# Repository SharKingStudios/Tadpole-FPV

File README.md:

# Tadpole FPV Drone
A small FPV drone that has a custom cost effective transmitter PCB.

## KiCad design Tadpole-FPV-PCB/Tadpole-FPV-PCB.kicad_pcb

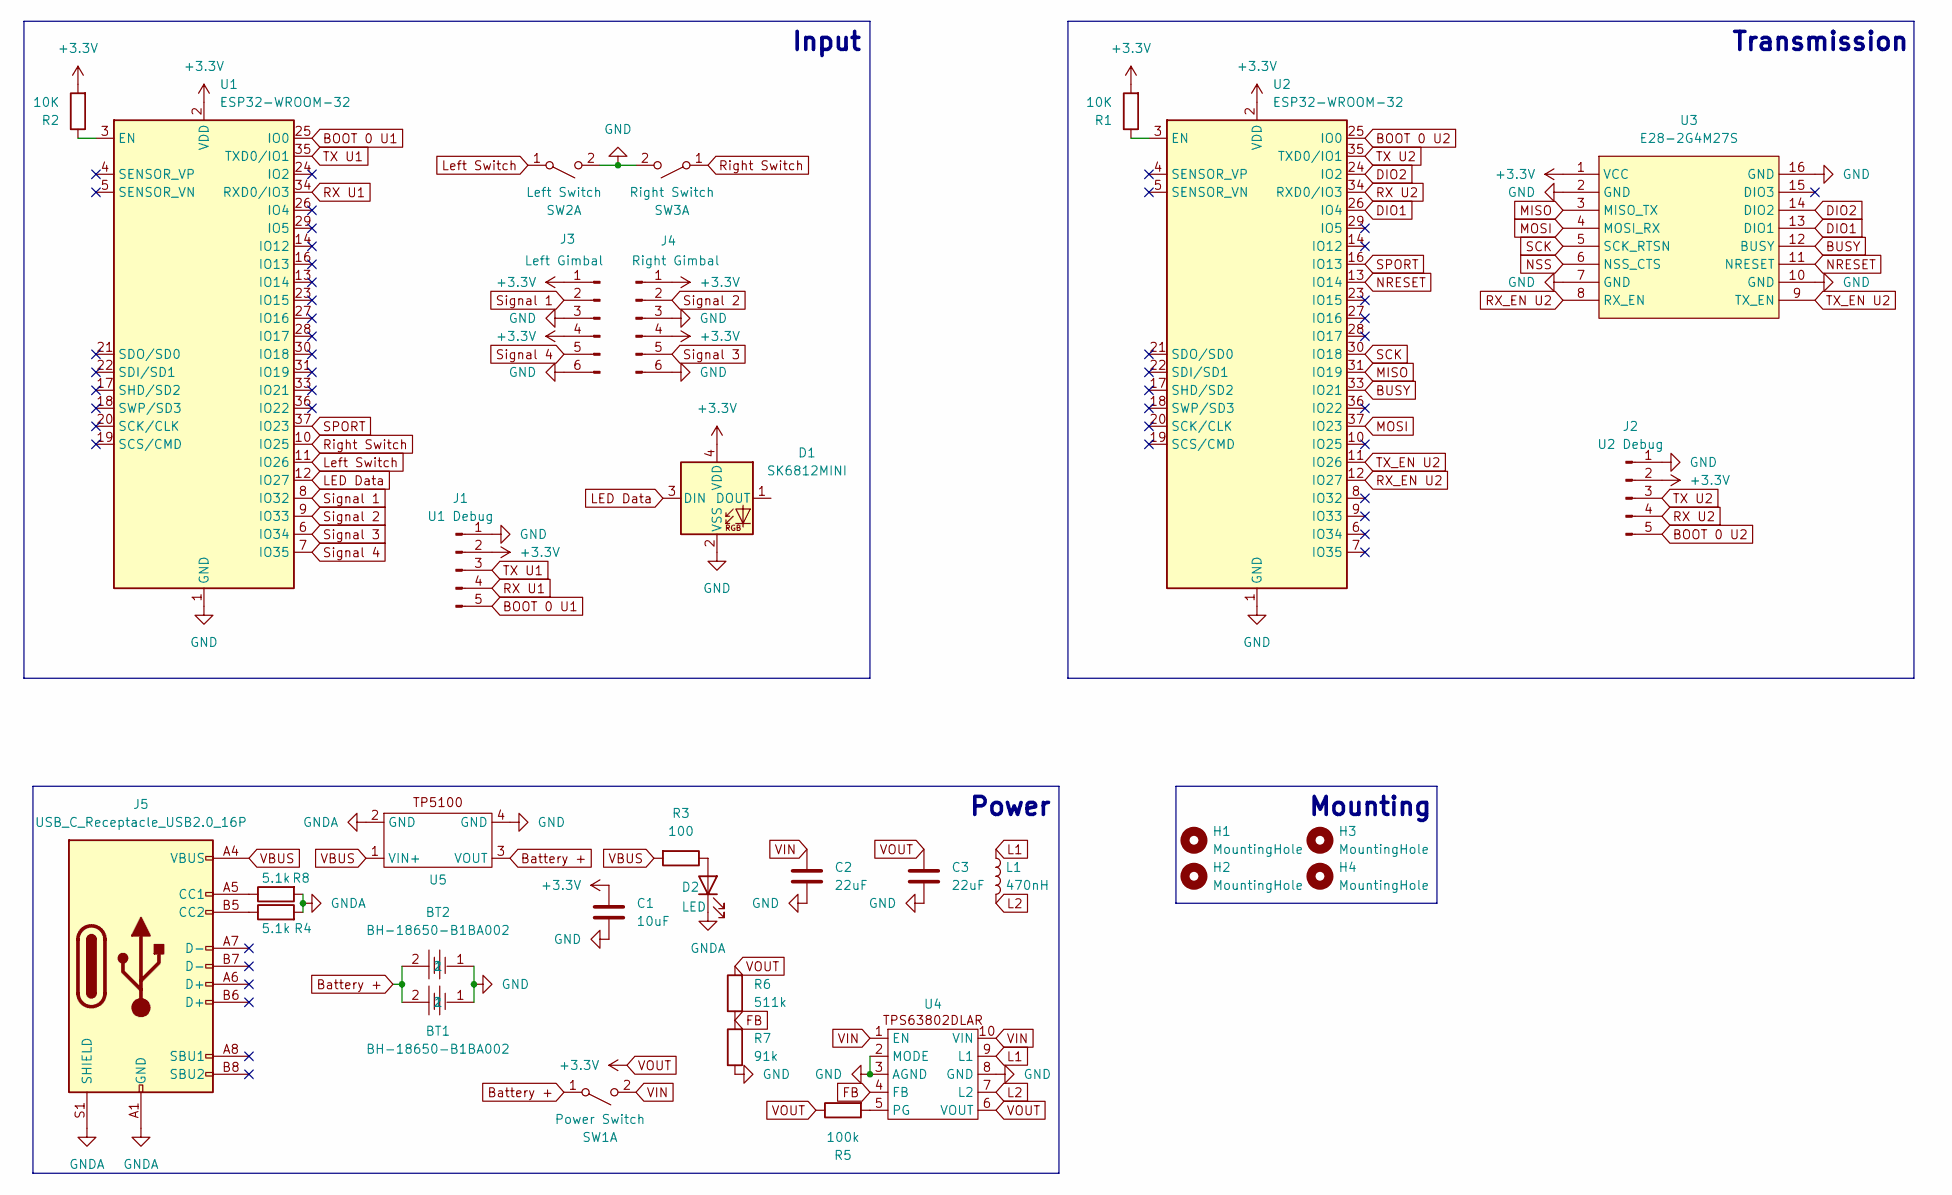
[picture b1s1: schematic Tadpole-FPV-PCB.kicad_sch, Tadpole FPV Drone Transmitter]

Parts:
BT1, BT2: BH-18650-B1BA002; BATTERY-SMD_18650-1S-L77.1-W20.7-1; LCSC Part C2988620
C1: 10uF; CP_Radial_D5.0mm_P2.50mm
C2, C3: 22uF; C_0603_1608Metric
D1: SK6812MINI; LED_SK6812MINI_PLCC4_3.5x3.5mm_P1.75mm
D2: LED; 0603 LED
H1, H2, H3, H4: MountingHole; MountingHole_3.2mm_M3_Pad_Via
J1: U1 Debug; PinHeader_1x05_P2.54mm_Vertical
J2: U2 Debug; PinHeader_1x05_P2.54mm_Vertical
J3: Left Gimbal; PinHeader_1x06_P2.54mm_Vertical
J4: Right Gimbal; PinHeader_1x06_P2.54mm_Vertical
J5: USB_C_Receptacle_USB2.0_16P; USB_C_Receptacle_GCT_USB4105-xx-A_16P_TopMnt_Horizontal
L1: 470nH; IND-SMD_L4.0-W4.0_XGL4020
R1, R2: 10K; R_0603_1608Metric
R3: 100; R_0603_1608Metric
R4, R8: 5.1k; R_0603_1608Metric
R5: 100k; R_0402_1005Metric
R6: 511k; R_0402_1005Metric
R7: 91k; R_0603_1608Metric
SW1: Power Switch; PinHeader_1x02_P2.54mm_Vertical
SW2: Left Switch; PinHeader_1x02_P2.54mm_Vertical
SW3: Right Switch; PinHeader_1x02_P2.54mm_Vertical
U1, U2: ESP32-WROOM-32
U3: E28-2G4M27S; WIRELM-SMD_E28-2G4M2XS; LCSC Part C411312
U4: VSON-10_L3.0-W2.0-P0.50-TL
U5: TP5100

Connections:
BOOT 0 U1: J1.5, U1.25 (IO0)
BOOT 0 U2: J2.5, U2.25 (IO0)
BUSY: U2.33 (IO21), U3.12 (BUSY)
Battery +: BT1.2, BT2.2, SW1.1 (A), U5.3 (VOUT)
DIO1: U2.26 (IO4), U3.13 (DIO1)
DIO2: U2.24 (IO2), U3.14 (DIO2)
FB: R6.1, R7.2, U4.4 (FB)
GND: BT1.1, BT2.1, C1.2, C2.1, C3.2, D1.2 (VSS), J1.1, J2.1, J3.3, J3.6, J4.3, J4.6, R7.1, SW2.2 (B), SW3.2 (B), U1.1 (GND), U1.15 (GND), U1.38 (GND), U1.39 (GND), U2.1 (GND), U2.15 (GND), U2.38 (GND), U2.39 (GND), U3.2 (GND), U3.7 (GND), U3.10 (GND), U3.16 (GND), U4.2 (MODE), U4.3 (AGND), U4.8 (GND), U5.4 (GND)
GNDA: D2.1 (K), J5.A1 (GND), J5.A12 (GND), J5.B1 (GND), J5.B12 (GND), J5.S1 (SHIELD), R4.2, R8.2, U5.2 (GND)
L1: L1.1, U4.9 (L1)
L2: L1.2, U4.7 (L2)
LED Data: D1.3 (DIN), U1.12 (IO27)
Left Switch: SW2.1 (A), U1.11 (IO26)
MISO: U2.31 (IO19), U3.3 (MISO_TX)
MOSI: U2.37 (IO23), U3.4 (MOSI_RX)
NRESET: U2.13 (IO14), U3.11 (NRESET)
NSS: U3.6 (NSS_CTS)
unnamed: D2.2 (A), R3.1
unnamed: J5.A5 (CC1), R8.1
unnamed: J5.B5 (CC2), R4.1
unnamed: R2.1, U1.3 (EN)
unnamed: R1.1, U2.3 (EN)
unnamed: R5.2, U4.5 (PG)
RX U1: J1.4, U1.34 (RXD0/IO3)
RX U2: J2.4, U2.34 (RXD0/IO3)
RX_EN U2: U2.12 (IO27), U3.8 (RX_EN)
Right Switch: SW3.1 (A), U1.10 (IO25)
SCK: U2.30 (IO18), U3.5 (SCK_RTSN)
SPORT: U1.37 (IO23), U2.16 (IO13)
Signal 1: J3.2, U1.8 (IO32)
Signal 2: J4.2, U1.9 (IO33)
Signal 3: J4.5, U1.6 (IO34)
Signal 4: J3.5, U1.7 (IO35)
TX U1: J1.3, U1.35 (TXD0/IO1)
TX U2: J2.3, U2.35 (TXD0/IO1)
TX_EN U2: U2.11 (IO26), U3.9 (TX_EN)
VBUS: J5.A4 (VBUS), J5.A9 (VBUS), J5.B4 (VBUS), J5.B9 (VBUS), R3.2, U5.1 (VIN+)
VIN: C2.2, SW1.2 (B), U4.1 (EN), U4.10 (VIN)
VOUT: C1.1, C3.1, D1.4 (VDD), J1.2, J2.2, J3.1, J3.4, J4.1, J4.4, R1.2, R2.2, R5.1, R6.2, U1.2 (VDD), U2.2 (VDD), U3.1 (VCC), U4.6 (VOUT)

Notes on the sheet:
Mounting
Transmission
Input
Power

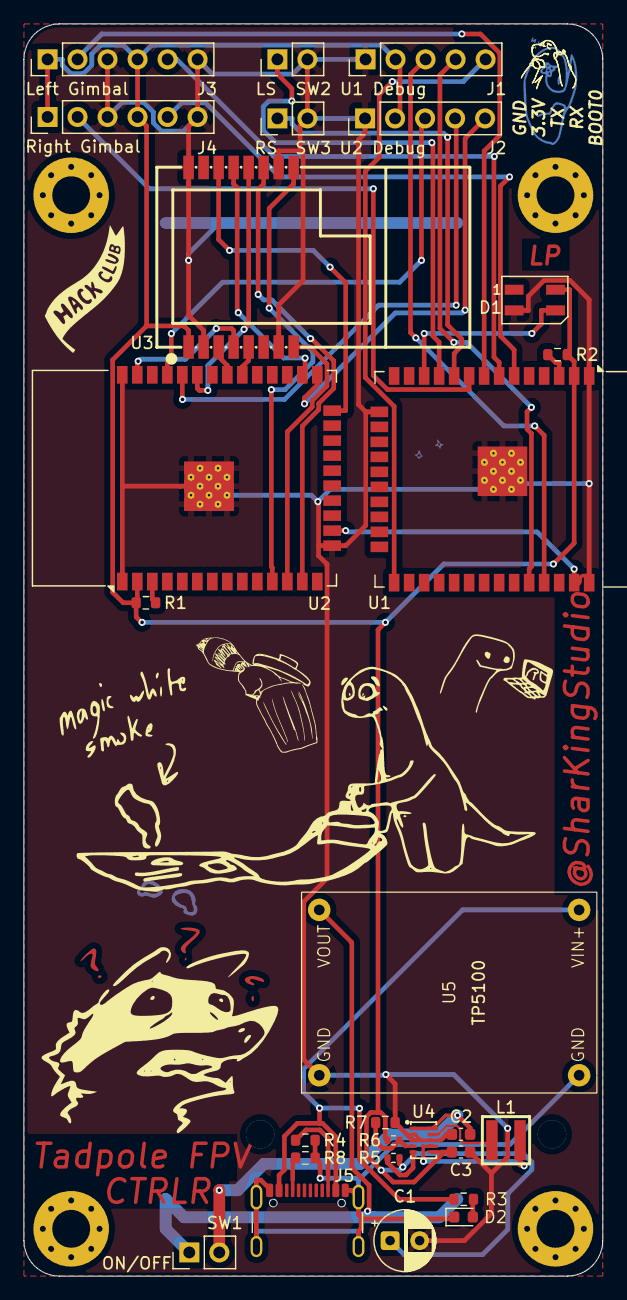
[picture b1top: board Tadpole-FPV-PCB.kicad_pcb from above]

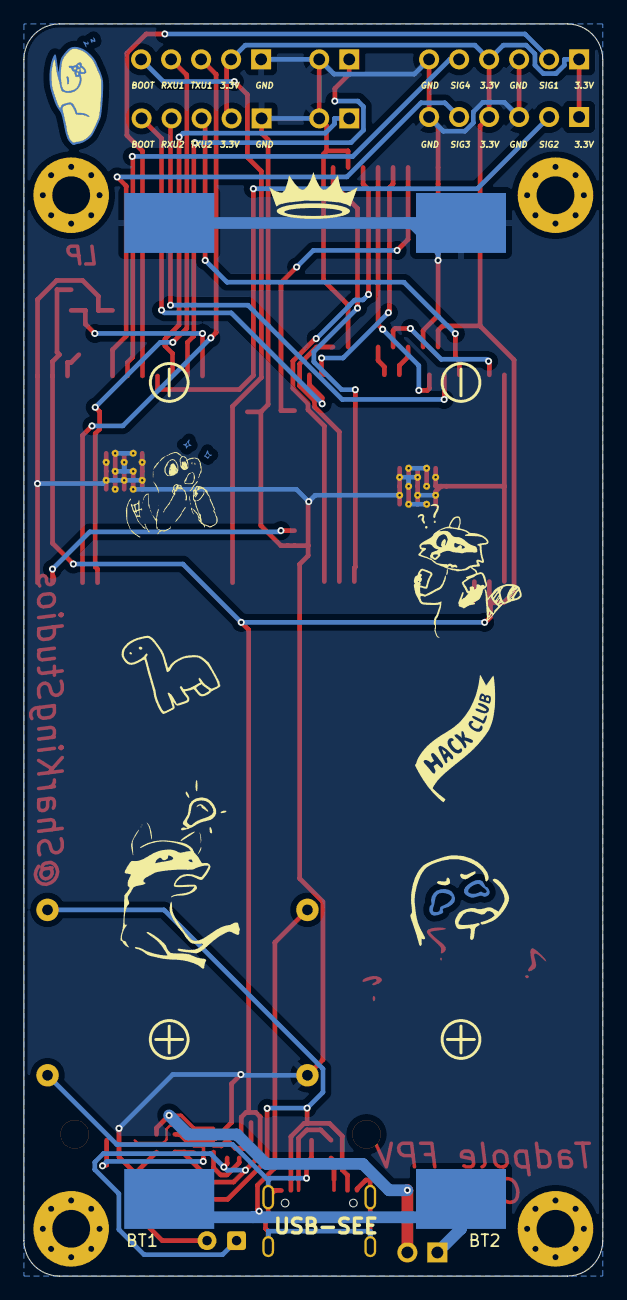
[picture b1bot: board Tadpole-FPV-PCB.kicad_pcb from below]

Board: 2 copper layers, 49.0 x 106.0 mm, 33 parts (2 on the bottom side), 38 nets.

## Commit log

2025-06-07 Drone Parts Selected + Work on Transmitter
    Lots a work
2025-06-07 Journal Consistency Fix
    Its a bit late...
2025-06-21 Finalized Transmitter Electronics
2025-06-23 Finished PCB Schematic Design
    Started PCB Design in KiCAD + Finished PCB Schematic Design
2025-06-24 Finished PCB Schematic Design (Again)
    I feel like this might happen a couple more times...
2025-06-26 Finished PCB Layout and Wiring + PCB Art!
    Also fixed some layout issues from earlier Journal entries.
